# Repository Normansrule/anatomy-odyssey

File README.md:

<div align="center">

# Anatomy Odyssey

**A wall chart of the human body that you can fall into, from two meters down to a single molecule.**

[**Open the web app**](https://normansrule.github.io/anatomy-odyssey/) ·
[Download the desktop app](https://github.com/Normansrule/anatomy-odyssey/releases/latest) ·
[Read the guide](https://normansrule.github.io/anatomy-odyssey/guide/) ·
[Features](#key-features) ·
[Setup](#setup-and-usage) ·
[Design](#design)

<a href="https://normansrule.github.io/anatomy-odyssey/">
<picture>
  <source media="(prefers-color-scheme: dark)" srcset="docs/media/hero-dark.webp" />
  
</picture>
</a>

</div>

## What it is

Anatomy Odyssey is a three-dimensional (3D) model of the human body, drawn like the anatomy charts that hung in every biology classroom, except this one zooms. Grab the scale on the left and drag: the view falls from the whole body (measured from a real person) into an organ, its tissue, one of its cells and finally the molecule that does the work, every plate at its real size. It's made for curious people, students and teachers who want to *see* how the body fits together across scales, not memorize a diagram. It runs in any current browser (phones included) or as a desktop app, with no accounts and no tracking.

> [!NOTE]
> It's a teaching model, not medical advice. Every scene says what it is (a generalized model, drawn to scale unless its card says otherwise) and cites its sources.

## Key features

- **Fifteen dives and six modules.** Skeletal, circulatory, muscular, immune, nervous, respiratory, digestive, urinary, endocrine, skin, eye, ear, pancreas, liver and smell, plus modules on inflammation, gene to protein, body chemistry, immune memory, T cells and the knee-jerk reflex. Every one ends at a molecule.
- **A body measured from a real one.** Meshes from BodyParts3D, an open anatomy atlas: every muscle and organ in its true place. The heart beats, blood flows through the vessels, and the organ close-ups are the real organs cut open.
- **A skeleton you'd find in a lecture hall.** 258 bones and teeth from Z-Anatomy, a finer, cleaned-up rebuild of that atlas, fitted back onto the body to within about a millimeter and shaded with the soft shadow each bone casts on itself: every foramen of the skull, every facet of the spine.
- **Read a heart scan.** A new step turns an ultrasound probe through the four standard echo views, the way trainee doctors learn them with teaching tools like Toronto's Virtual TEE: a fan of sound cuts the real heart, the heart turns to show you the slice, and a scanner screen beside it draws that slice as an echo machine would, grainy and beating, with an ECG running underneath.
- **One slider from 10 m to 0.1 nm.** The scale on the left is a slider. Drag it (or use the arrow keys) and the view zooms continuously, flying on to the next plate whenever you get close to its size, so a single drag can take you from your whole body to DNA.
- **Labeled like a wall chart.** Every part in view is named at the edge of the plate with a line to the part, and numbered in the card's key. Point at a label, a part or a key entry and a red leader line lights up, following the part as the model turns.
- **Zoom in anywhere.** Scroll or pinch toward any part of the body; a guide names the nearest part that has a dive and takes you there.
- **Point, click, learn.** Hover to name a part, click to open its card: what it does, why it matters, its real size, an *Expert detail* switch and a source you can check.
- **Labeled like a lecture-hall chart.** The skeleton names every major bone (skull, jaw, collarbone and shoulder blade, breastbone, humerus, radius, ulna, femur, kneecap, tibia, fibula and the bones of the hand and foot), and the muscular dive names every muscle in the body: the big ones each have a card, and the rest are filed in 20 regional groups the way an atlas's plates are (the face, the jaw, the hyoid, the deep neck, the back, the chest and belly walls, the rotator cuff and shoulder blade, the forearm, hand, hip, thigh, leg and foot), each with what it does and the clinical facts students meet first. The circulatory dive names the vessels by region: the carotid and jugular, subclavian, gut, iliac and limb vessels. Each has its own card, and a chart holds up to 24 labels, set in two balanced columns; an organ dive's chart names its own organs and only a few landmarks around them.
- **By the numbers.** Every whole-body, system and organ plate prints its headline figure under the heading (100,000 heartbeats a day, 86 billion neurons, 480 million alveoli), and the card opens on three big figures that count up as it appears, 64 cards in all, each a typical adult value from the card's sources.
- **Light sheet or slate.** It follows your device's light or dark setting, or pick one in About.
- **Science you can play with.** Sliders run real, tested equations (oxygen binding, nerve speed, blood acidity, how fast an enzyme works, how much blood the heart pumps).
- **A map by scale, a tour, quizzes and a glossary.** The map (press M) lays out every dive on one size axis; the tour narrates a dive with captions you can have read aloud.
- **Front and back plates.** A button under the whole body turns it round, as a wall chart comes as a front and a back plate: the labels move to the parts seen from behind (trapezius, latissimus dorsi, the deep back muscles, the rotator cuff, gluteus maximus, the hamstrings), and each sits on the surface that faces you.
- **Take it apart.** "Take apart" lifts each body system out of the whole and stands them in a row, skin first, then muscle, bone, nerves, blood vessels, lungs, gut, kidneys, glands and the immune system, each on its own floor shadow with its name underneath, the way an exploded diagram lays out a machine. Each figure steps out on a spring, a beat after the one before; "Put together" walks them back in reverse. The row turns round with "See the back" too. Point at a system in the row and it lifts off the floor; each caption gives the system's headline figure and opens its card. Standing alone, the skin fills in to a solid figure. Press A to take it apart and B to turn it round.
- **Named nerves.** The sciatic nerve and its tibial and common fibular branches, the femoral, the brachial plexus, the median, ulnar and radial nerves and both vagus nerves run where they do in life, in atlas yellow, each opening its own card.
- **Sound, if you want it.** Off by default. Turn it on and toggles tick, cards pop, the body breathes as it comes apart, and each plate chimes lower the deeper you go. Every sound is synthesized in the browser, with no files and no downloads.
- **A stage and a measuring rod.** The body stands on a turntable plinth with an engraved dial, beside a stadiometer whose headboard rests on the crown at 1.64 m, and its lungs breathe 14 times a minute.
- **Made to move.** After every flight the plate sets itself like a printed chart: the heading rises out of its baseline and each label's line draws out from its part. The studio light follows your pointer across the model, and the guide's landing page falls through the body as you scroll.
- **A guide website.** A landing page drawn as the same chart, plus the docs as a printed booklet, at [/guide/](https://normansrule.github.io/anatomy-odyssey/guide/).
- **Private and accessible.** No network calls after loading, full keyboard control, screen-reader announcements, a reduced-motion mode, and an automated Web Content Accessibility Guidelines (WCAG) 2.2 audit with zero violations in 55 states, light and dark.

## See it

<table>
<tr>
<td align="center" width="50%"><br /><sub><b>A labeled skeleton.</b> Every major bone named at the plate's edge, the arm and leg bones each with its own card.</sub></td>
<td align="center" width="50%"><br /><sub><b>A labeled muscle chart.</b> Every muscle on the real body opens a card: the big ones their own, the rest their group's.</sub></td>
</tr>
<tr>
<td align="center" width="50%"><br /><sub><b>The back plate.</b> Turn the body round and the chart names what you see from behind.</sub></td>
<td align="center" width="50%"><br /><sub><b>Take it apart.</b> The systems step out of the body one by one and stand in a row, outside in.</sub></td>
</tr>
<tr>
<td align="center" colspan="2"><br /><sub><b>Named nerves.</b> The nerves an anatomy course names first, in atlas yellow, front and back.</sub></td>
</tr>
<tr>
<td align="center" colspan="2"><br /><sub><b>On its stand.</b> A turntable plinth and a stadiometer give the figure a place to stand and a height to read.</sub></td>
</tr>
<tr>
<td align="center" colspan="2"><br /><sub><b>By the numbers.</b> Each plate prints its headline figure, and each card opens on three.</sub></td>
</tr>
<tr>
<td align="center" colspan="2"><br /><sub><b>Read a heart scan.</b> Turn the probe through the four standard views and match each echo picture to the real heart.</sub></td>
</tr>
<tr>
<td align="center" width="50%"><br /><sub><b>258 real bones.</b> Z-Anatomy's skeleton, fitted to the body to a millimeter.</sub></td>
<td align="center" width="50%"><br /><sub><b>One slider, 10 m to 0.1 nm.</b> A single drag takes you from your whole body to DNA.</sub></td>
</tr>
<tr>
<td align="center" colspan="2"><br /><sub><b>Fall through the body.</b> Scroll the guide and drop from your whole body to a strand of DNA.</sub></td>
</tr>
<tr>
<td align="center" colspan="2"><br /><sub><b>The plate sets itself.</b> After every flight the heading rises and each callout draws out from its part.</sub></td>
</tr>
<tr>
<td align="center" colspan="2"><br /><sub><b>The living key.</b> Point at an entry and its leader line draws to the part.</sub></td>
</tr>
<tr>
<td align="center" width="50%"><br /><sub><b>Heartbeat.</b> The measured heart opened to its four chambers; set the rate from asleep to running.</sub></td>
<td align="center" width="50%"><br /><sub><b>The guide.</b> The same chart as a website, with the docs as its booklet.</sub></td>
</tr>
<tr>
<td align="center"><br /><sub><b>Digestion.</b> One meal through the real gut, with how long each part takes.</sub></td>
<td align="center"><br /><sub><b>Urine.</b> From the blood, down the ureters, into the bladder and out.</sub></td>
</tr>
</table>

<table>
<tr>
<td><br /><sub>Whole body</sub></td>
<td><br /><sub>Heart scan</sub></td>
<td><br /><sub>Brain</sub></td>
<td><br /><sub>Lungs</sub></td>
</tr>
<tr>
<td><br /><sub>Liver</sub></td>
<td><br /><sub>Kidney</sub></td>
<td><br /><sub>Femur</sub></td>
<td><br /><sub>Map by scale</sub></td>
</tr>
</table>

### Progress

| Dive | Organ step | What moves | State |
|---|---|---|---|
| Skeletal | measured skeleton (258 Z-Anatomy bones); femur cut open | | Done |
| Circulatory | measured heart, four chambers; heart scan in the four echo views | heartbeat, blood flow, heart rate, the probe turning | Done |
| Respiratory | measured lungs and bronchial tree | breathing | Done |
| Nervous | measured brain, lobes and inside | | Done |
| Digestive | measured tract, esophagus to rectum | a meal moving through | Done |
| Urinary | measured kidneys, ureters and bladder; kidney cut open | urine flow, bladder filling | Done |
| Pancreas | measured pancreas with duct and islets | | Done |
| Liver | measured liver with veins and bile ducts | blood and bile flow | Done |
| Immune | lymph node, drawn | an infection from a cut to the armpit nodes | Body done, close-up drawn |
| Muscular | biceps, drawn and cut across | | Next candidate |
| Skin | skin block, drawn | heat and cold | Drawn close-up |
| Smell | nasal cavity, drawn | a sniff | Drawn close-up |
| Endocrine | thyroid, drawn | | The atlas has no thyroid |
| Eye | eye, drawn | light focusing | The atlas eye is too coarse |
| Ear | ear, drawn | sound | The atlas has the outer ear only |

<details>
<summary><b>More screenshots</b>: every organ, cell and molecule step</summary>

<table>
<tr>
<td></td>
<td></td>
<td></td>
</tr>
<tr>
<td></td>
<td></td>
<td></td>
</tr>
<tr>
<td></td>
<td></td>
<td></td>
</tr>
<tr>
<td></td>
<td></td>
<td></td>
</tr>
<tr>
<td></td>
<td></td>
<td></td>
</tr>
<tr>
<td></td>
<td></td>
<td></td>
</tr>
<tr>
<td></td>
<td></td>
<td></td>
</tr>
<tr>
<td></td>
<td></td>
<td></td>
</tr>
<tr>
<td></td>
<td></td>
<td></td>
</tr>
<tr>
<td></td>
<td></td>
<td></td>
</tr>
<tr>
<td></td>
<td></td>
<td></td>
</tr>
<tr>
<td></td>
<td></td>
<td></td>
</tr>
<tr>
<td></td>
<td></td>
<td></td>
</tr>
<tr>
<td></td>
<td></td>
<td></td>
</tr>
</table>

| Nervous dive | Respiratory dive |
|---|---|
|  |  |

</details>

## Setup and usage

### Just use it

| Version | Where | Notes |
|---|---|---|
| **Web** | [normansrule.github.io/anatomy-odyssey](https://normansrule.github.io/anatomy-odyssey/) | Any current browser, phones included. Nothing to install. |
| **Desktop** | [Latest release](https://github.com/Normansrule/anatomy-odyssey/releases/latest) | Windows `.exe`/`.msi`, macOS `.dmg`, Linux `.AppImage`/`.deb`. Not code-signed yet, so the first launch shows a warning. |

Pick a dive from the menu at the top (or a part of you on the first screen). Then either drag the scale on the left, or use **Dive deeper** and **Zoom out** on the row of plates at the bottom. Scroll or pinch to zoom, drag the view to turn it, and point at a number in the key to see where that part is. Press **M** for the map, and try **Play tour** for a narrated run-through.

| Key | What it does |
|---|---|
| Arrow keys or Page Up and Page Down on the scale | Zoom by a quarter (or a whole) power of ten |
| Home and End on the scale | Jump to 10 m or to 0.1 nm |
| Left and right arrows elsewhere | The previous or next plate |
| `/` | Search |
| `M`, `G`, `T` | The map, the glossary, the tour |

### Run it yourself

You'll need [Node.js](https://nodejs.org) 20 or newer.

```bash
git clone https://github.com/Normansrule/anatomy-odyssey.git
cd anatomy-odyssey
npm ci
npm run dev          # then open http://localhost:5173
```

<details>
<summary><b>More commands</b>: tests, builds, desktop app, screenshots</summary>

```bash
npm test               # 528 unit tests, plus the asset manifest check
npm run build          # production build in dist/ (what GitHub Pages serves), with the guide in dist/guide/
npm run build:preview  # one self-contained HTML (HyperText Markup Language) file in dist-preview/
npm run molecules      # regenerate molecule geometry (needs: pip install rdkit)
python3 tools/record-hero.py --dive skeletal --slide 1e-8 --width 860 --out docs/media/scale-slider.gif
                       # record a README animation (see the file for the other modes; needs Playwright)
python3 tools/build_body_meshes.py --fetch && python3 tools/build_body_meshes.py && npm run manifest
                       # rebuild the body anatomy from BodyParts3D (needs: pip install numpy fast-simplification)
python3 tools/zanatomy_skeleton.py --fetch && python3 tools/zanatomy_skeleton.py
python3 tools/build_body_meshes.py --skeleton tools/sources/zanatomy/skeleton.npz --from-bundle && npm run manifest
                       # swap in Z-Anatomy's skeleton with baked shading (needs: pip install bpy==4.2.0, Python 3.11)
```

**Desktop app** (needs [Rust](https://rustup.rs); on Linux also `sudo apt install libwebkit2gtk-4.1-dev build-essential libssl-dev libayatana-appindicator3-dev librsvg2-dev`):

```bash
npm run desktop:dev      # native window with live reload
npm run desktop:build    # installers in src-tauri/target/release/bundle/
```

Pushing a version tag (`git tag v0.22.0 && git push origin v0.22.0`) builds Windows, macOS and Linux installers and publishes them as a GitHub release. They aren't code-signed yet.

**Headless checks** (software rendering, no graphics card needed):

```bash
npm run build && npx vite preview --port 4173 &
pip install playwright pillow && python3 -m playwright install chromium
python3 tools/screenshots.py --mobile    # every step; fails on console errors or a blank view
python3 tools/a11y-audit.py              # axe-core accessibility audit, WCAG 2.2 A and AA, app and guide, light and dark
python3 tools/shoot-guide-body.py        # redraw the guide's body picture and measure where each dive starts on it
python3 tools/shoot-guide-fall.py        # redraw the cut-out plates for the guide's "Fall through the body"
python3 tools/record-motion.py fall      # record the README's motion animations (fall, plate, scan or skeleton)
python3 tools/shoot-readme-hero.py       # redraw the README's poster, light and dark
```

**Web address options**: `?dive=nervous&step=synapse` opens a step, `&trip=1` opens a side trip, `?renderer=webgl` forces the WebGL 2 fallback, `?env=0` turns off studio reflections.

**Publishing**: [docs/PUBLISHING.md](docs/PUBLISHING.md) has the exact terminal commands to apply a change, push it, turn on GitHub Pages and publish the desktop apps.

</details>

## Project structure

```
src/
  main.js      app start-up: wires the engine, the scenes and the interface together
  engine/      renderer (WebGPU, with a WebGL 2 fallback), tier engine, lighting, device check
    textures/  tissue surfaces generated in code: tileable noise, tissue recipes, materials
  scenes/      one builder per step (body, femur, heart, neuron, lungs, …) plus the registry
  library/     shared building blocks (nucleus, DNA, hemoglobin, ATP, …) and molecule data
  data/        dives, library graph, cards, quizzes, references: all the content lives here
  science/     pure, tested math: scale, equations, chemistry, immune model, T cells, reflexes
  ui/          scale slider, living key, cards, search, controls, tour, quiz, glossary, map, about
  styles/      app.css, the whole visual system (tokens at the top)
guide/         the guide website's stylesheet, script and body picture
src-tauri/     desktop shell (Tauri 2)
assets/        the measured body and molecule files, with credits
tests/         Vitest suites
tools/         guide builder, its Markdown converter and body picture, screenshots, accessibility audit,
               animation recorder, mesh and molecule builders
docs/          state of the model, equations, security model, publishing, media
```

Each dive is a **chain of scenes**, each built at its own scale (1 unit = 1 m for the body, 1 cm for organs, 1 µm for cells, 1 nm or 1 Å for molecules), because the gap from body to molecule is about a billion-fold. The engine frames each scene by its real size and flies between them while the scale slider sweeps on a log scale.

<details>
<summary><b>Adding a dive</b></summary>

1. Write scene builders in `src/scenes/` (return `root`, `metersPerUnit`, `view`, `focus`, `dispose`; optionally `controls`, `update`, `branchFocus`).
2. Register them in `src/scenes/registry.js` and add the dive to `src/data/dives.js`.
3. Tag tissue materials for realistic surfaces: `M(color, { tissue: 'muscle' })` (the kinds are in `src/engine/textures/tissues.js`).
4. Write cards with sources, narration for each step, and four quiz questions.
5. `npm test` checks that frames shrink and tiers rise, every clickable part has a card, and shared steps reuse the library.

</details>

## Design

**The idea: a classroom wall chart.** You know the ones: a pull-down anatomy chart with heavy rules, numbered leader lines running to a key, and the parts colored by a code every textbook shares. Anatomy Odyssey is that chart, with two things paper can't do: the specimen is a live 3D model, and the chart zooms.

- **The sheet is ruled into cells.** The scale column on the left, the plate in the middle, the key on the right, and the plates of the dive along the bottom, all divided by 2-pixel rules like a printed chart. The plate itself sits inside a double-ruled frame, under a heading set the way a chart prints one: a red rubric ("Plate 2 of 6 · Organ tier"), the subject in huge condensed capitals, and the dive it belongs to. No floating cards, no frosted glass, no drop shadows.
- **Every color means something anatomical.** Artery red, vein blue, nerve yellow, lymph green and bone ivory, the code anatomy charts have always used. Red also means "you are here": the scale's marker, the current plate, the one main action and the leader line you're tracing. Vein blue marks focus and links. Nothing gets a color just to decorate.
- **Light sheet or slate.** Light mode is the printed sheet: warm, uncoated paper with a fine grain. Dark mode is the same chart on slate. Every text color is at least 4.5 to 1 against its background in both.
- **Two typefaces, each with one job.** Archivo, condensed and heavy, for plate titles and numbers, like the lettering on a chart; Atkinson Hyperlegible Next, designed for low-vision readers, for everything you read. Nothing is smaller than 12 pixels, and numbers are tabular so they don't jitter while the slider moves.
- **One spacing rhythm.** Every gap is a multiple of 4 pixels, and every target you can press is at least 24 pixels (44 for the main controls).

**The hero moment is the scale slider.** Drag it and the view follows your finger seamlessly: inside a plate the camera zooms on a spring (on a log scale, so every power of ten takes the same time), and when the size you're asking for is closer to the next plate's, the view flies on and keeps going. The flight speeds up out of one plate and slows into the next, so there's no stop in the middle where the model swaps.

**The second is the living key.** On a wide screen the plate is labeled the way a printed chart is: every part's name is set in a column at the plate's edge, with a hairline running to a dot on the part. The labels are projected from the 3D parts every frame, stacked a row apart and centered on their parts so the lines stay short, and they follow the model as you turn it. Point at a label or a key entry and its line turns red; on a phone each part carries a numbered mark instead.

**Then the plate sets itself.** Big product pages earn their polish with motion that explains: a scroll that tells a story, light that answers the pointer, type that arrives instead of appearing. The chart borrows those, in its own printed voice. The neatline rules itself around the plate on the first visit. After every flight the heading rises out of its own baseline and the callouts draw out from their parts one by one, each label reading in from the end its line arrives at, so your eye goes from the part to its name. The studio lights ride with the camera like a photographer's, and the key light leans toward your pointer, so highlights slide across the model as you explore. On the guide, "Fall through the body" pins a stage to the screen and lets your scroll drive the dive: each plate grows past you and fades as the next, smaller one rises out of it, while a needle falls down the ruler and the view height counts down.

**Motion has a job or it doesn't happen.** Buttons answer a press with a slight 0.97 scale in 140 milliseconds, easing out so they feel immediate. Hover effects only switch on for a real mouse, so taps never leave a stuck highlight. With reduced motion on, flights become a short crossfade, the slider and leader lines jump instead of springing, headings and callouts simply appear, the light stays put, the guide shows its plates as a plain row, and nothing slides or scales, but color and fade feedback stay so you still see what happened.

**States are designed too.** Loading shows a ruled "Drawing the plate" title card while the 15 megabyte body loads; if the measured body can't load, a notice says the simplified figure is showing; a browser without 3D graphics gets a plain explanation instead of a blank page; and an empty search suggests what to try.

The whole visual system is the token block at the top of [`src/styles/app.css`](src/styles/app.css), and the guide website reads its tokens from the same file.

## Documentation

All of these are also on the [guide website](https://normansrule.github.io/anatomy-odyssey/guide/), set as the chart's booklet.

| Document | What's inside |
|---|---|
| [State of the model](docs/STATE_OF_THE_MODEL.md) | Every step, where it honestly stops, and what is simplified |
| [Equations](docs/EQUATIONS.md) | 29 worked examples, each with symbols, units and its test |
| [Security model](docs/SECURITY_MODEL.md) | Trust boundaries, privacy (a strict Content Security Policy, no analytics), supply chain |
| [Publishing](docs/PUBLISHING.md) | Apply a change, push it, turn on the website, publish the desktop apps |
| [Changelog](CHANGELOG.md) | What changed in each version |
| [Asset credits](assets/CREDITS.md) | Sources and licenses |

## Roadmap

- [x] Fifteen dives, six modules and a complete shared library; every dive and every module ends at a molecule
- [x] Desktop app, device check, accessibility audit
- [x] Realistic tissue surfaces with natural and stain looks
- [x] A body measured from a real one, and real organs for the heart, brain, lungs, liver, pancreas, kidney, femur and the digestive and urinary tracts
- [x] A wall chart redesign: the scale slider, the living key, light and dark sheets, and a guide website
- [ ] Measured thyroid, eye and ear
- [ ] Real atomic structures from the Protein Data Bank for the large molecules
- [ ] Code-signed desktop releases

## License

- **Code**: [MIT License](LICENSE).
- **Anatomy assets** in `assets/anatomy/`: derived from BodyParts3D, Creative Commons Attribution-ShareAlike 2.1 Japan (CC BY-SA 2.1 JP), with the skeleton from Z-Anatomy by Lluís Vinent and Gauthier Kervyn (CC BY-SA 4.0); see [assets/CREDITS.md](assets/CREDITS.md). ShareAlike covers those files only.
- **Molecular assets**: each file's own license, listed in [assets/CREDITS.md](assets/CREDITS.md).
- **Fonts**: Archivo and Atkinson Hyperlegible Next, SIL Open Font License 1.1, served from the app itself.
- Tissue textures are generated in code and covered by the MIT License.

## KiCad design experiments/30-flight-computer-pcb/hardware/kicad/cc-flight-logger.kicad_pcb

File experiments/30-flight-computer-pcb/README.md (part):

# 30 · Flight-computer PCB — a hand-solderable rocket data logger in KiCad

**Level 3 · stage 3** — design, build and test **CC-FL1**, an 80 × 30 mm printed circuit board that
rides inside a 38 mm airframe and records a rocket flight at 100 samples per second: a Bosch BMP390
barometer, an ST LSM6DSO32 ±32 g inertial measurement unit (IMU), a microSD card, a Li-Po charger,
a beeper and a header for the LoRa radio of [experiment 31](../31-lora-telemetry-ground-station/).
The brain is a **Raspberry Pi Pico** soldered flat by its castellated edge, so there is no
0.4 mm-pitch microcontroller to solder. You get a complete KiCad project generated from one Python
file, firmware with a Kalman filter and a flight state machine, a host-side test harness that
"flies" the real firmware through synthetic flights, and a 3D-printed sled.

It is the natural next step after [experiment 22](../22-barometric-altimeter-payload/) (Pico + BMP390
on a breadboard, MicroPython): same idea, now as a real board, in C++, with sensor fusion.

| Cost | Time | Difficulty | Ages |
|---|---|---|---|
| **$45–110** (boards $5–25, parts $30–45, optional sensor assembly $15–30, Li-Po + card $12) | **20–35 h** (routing 3–5 h, assembly 3 h, firmware + tests 6 h, flight day) | ●●●●○ | 15+; flights at a club launch |

> [!CAUTION]
> **This is a data logger, not a recovery controller.** The board has no outputs that fire anything,
> and none should be added. If a flight needs electronic recovery deployment, that is done by a
> **certified commercial altimeter**, and flying such rockets requires high-power certification and
> mentorship ([experiment 40](../40-high-power-rocketry-certification/)). Fly only
> **commercially certified motors**, at a club launch under a Range Safety Officer, following the NAR or
> Tripoli safety code ([../SAFETY.md](../SAFETY.md)). Li-Po cells: charge on a non-flammable surface,
> never puncture or short them, and store them at ~3.8 V.

## What you'll learn

- **Schematic capture and PCB layout in KiCad**, from a design described as *data* (`design.py`) —
  symbols, footprints, nets, net classes, design-rule checks (DRC), and why placement decides routing.
- **Power design** for a battery gadget: USB-C sink detection, a linear Li-Po charger,
  diode OR-ing, a low-dropout (LDO) regulator, dropout and thermal budgets.
- **Sensor physics**: why a barometer measures altitude, what an accelerometer *really* measures
  (specific force, not acceleration), and how the two are fused with a **Kalman filter**.
- **Real-time firmware** on a dual-core RP2040: a 100 Hz control loop on core 0, a lock-free queue to
  a microSD writer on core 1, a flight **state machine**, and a non-blocking beeper.
- **Testing without flying**: a physics-based synthetic flight generator and a C++ host harness that
  runs the exact firmware logic against ground truth — the way aerospace flight software is tested.
- **Manufacturing**: generating gerbers, choosing assembly options at JLCPCB/PCBWay, reflowing
  land-grid-array (LGA) sensors.

## What is in this folder

```text
30-flight-computer-pcb/
├── hardware/
│   ├── kicad/                  KiCad project (cc-flight-logger.kicad_pro/.kicad_sch/.kicad_pcb)
│   │   ├── cosmic_codex.kicad_sym   project symbols: Pico, BMP390, LSM6DSO32
│   │   └── cosmic_codex.pretty/     project footprints: Pico (hand-solder), BMP390 LGA-10
│   ├── scripts/
│   │   ├── design.py           ← the single source of truth: parts, pins → nets, placement
│   │   ├── make_library.py     writes the project symbols/footprints
│   │   ├── generate.py         writes schematic, board (via KiCad's pcbnew) and BOM.csv
│   │   ├── check.py            asks KiCad for the netlist + DRC and verifies them against design.py
│   │   ├── plot_board.py       placement + ratsnest picture
│   │   └── export_fab.sh       gerbers / drill / pick-and-place / BOM (after routing, KiCad 8+)
│   ├── BOM.csv                 bill of materials with manufacturer + LCSC/DigiKey numbers
│   ├── cc-flight-logger-schematic.pdf
│   ├── ROUTING.md              the routing exercise, step by step
│   └── ORDERING.md             JLCPCB / PCBWay ordering and assembly guide
├── firmware/
│   ├── flight_logger/          Arduino-Pico sketch: flight_logger.ino, flight_core.{h,cpp}, config.h,
│   │                           nmea.h, telemetry_packet.h
│   └── test/                   host test harness (make), mock Arduino headers
├── cad/avionics_sled.scad      OpenSCAD sled for a 38 mm tube  → stl/avionics_sled.stl, stl/nose_bulkhead.stl
├── tools/synth_flight.py       synthetic flight + sensor generator
├── tools/plot_flight.py        plot any flight log
├── data/                       a synthetic flight (sensor input, truth, and the replayed log)
└── images/
```

## System overview

```mermaid
flowchart LR
    USBC["USB-C<br/>(charge only)"] -->|VBUS_C| D1[SS14]
    D1 -->|VBUS| CHG["MCP73831<br/>Li-Po charger<br/>213 mA"]
    PICOUSB["Pico micro-USB<br/>(program + data)"] -->|VBUS| CHG
    CHG -->|+BATT| BAT[("1S Li-Po<br/>JST-PH")]
    BAT --> SW["J3 arming<br/>switch"]
    SW -->|VBAT_SW| D2[SS14] -->|VSYS| PICO["Raspberry Pi Pico<br/>RP2040"]
    D2 -->|VSYS| LDO["AP2112K<br/>3.3 V, EN = GP22"]
    LDO -->|+3V3| BARO["BMP390<br/>barometer"]
    LDO -->|+3V3| IMU["LSM6DSO32<br/>±32 g IMU"]
    LDO -->|+3V3| SD[("microSD")]
    PICO <-->|"I2C0 400 kHz"| BARO
    PICO <-->|I2C0| IMU
    PICO <-->|"SPI0"| SD
    PICO -->|"SPI1"| RADIO["J5 → RFM95W<br/>(exp. 31)"]
    PICO <-->|UART0| GPS["J6 → GPS"]
    PICO -->|GP15| BZ["piezo beeper"]
    PICO -->|GP14| LED[status LED]
    SW -->|"÷2"| PICO
```

## Bill of Materials

Full list with footprints and distributor numbers: [`hardware/BOM.csv`](hardware/BOM.csv) (generated
from `design.py`). Prices are typical single-quantity US prices in 2026 — check on the day.

| Ref | Qty | Part | Manufacturer part number (MPN) | LCSC | Approx. |
|---|---|---|---|---|---|
| U1 | 1 | Raspberry Pi Pico (Pico W also fits) | SC0915 | — (buy from an approved reseller) | $4 |
| U3 | 1 | 6-axis IMU, ±32 g, LGA-14L 2.5 × 3 mm | ST LSM6DSO32TR | search MPN | $4–6 |
| U4 | 1 | Barometer, LGA-10 2 × 2 mm | Bosch BMP390 | search MPN | $3–5 |
| U2 | 1 | Li-Po charger 4.20 V, SOT-23-5 | Microchip MCP73831T-2ACI/OT | C424093 | $0.70 |
| U5 | 1 | 3.3 V 600 mA LDO, SOT-23-5 | Diodes Inc AP2112K-3.3TRG1 | C51118 | $0.30 |
| J1 | 1 | USB-C receptacle, 6-pin power-only | GCT USB4125-GF-A | search MPN | $0.80 |
| J4 | 1 | microSD socket, push-push, card detect | Hirose DM3AT-SF-PEJM5 | search MPN | $1.50 |
| J2 | 1 | JST-PH 2-pin vertical header | JST B2B-PH-K-S(LF)(SN) | search MPN | $0.20 |
| J3, J7 / J6 / J5 | 2 / 1 / 1 | 2.54 mm SMD pin headers 1×2 / 1×4 / 1×8 | generic | — | $1 |
| BZ1 | 1 | piezo sounder 4 kHz, 12 × 12 mm SMD | Murata PKLCS1212E4001-R1 | search MPN | $1.50 |
| Q1 | 1 | NPN transistor, SOT-23 | MMBT3904 | C20526 | $0.05 |
| D1, D2 | 2 | Schottky 40 V 1 A, SMA | SS14 | C2480 | $0.10 |
| D4 | 1 | switching diode, SOD-123 | 1N4148W | C81598 | $0.05 |
| D3 / D5 | 1 / 1 | LED 0805 green / red | KT-0805G / KT-0805R | C2297 / C84256 | $0.10 |
| R1–R16 | 16 | 0805 resistors 1 %: 5.1k ×2, 4.7k ×3, 1k ×4, 100k ×3, 10k ×4 | UNI-ROYAL 0805W8F… | C27834 · C17673 · C17513 · C17407 · C17414 | $0.50 |
| C1–C11 | 10 | 0805 MLCC: 4.7 µF ×2, 10 µF ×2, 1 µF ×1, 100 nF ×5 | Samsung CL21… | C1779 · C15850 · C28323 · C49678 | $0.50 |
| — | 1 | 1S Li-Po 3.7 V ≈ 400 mAh, 8 × 25 × 40 mm ("802540"), with protection circuit, JST-PH lead | — | — | $6–10 |
| — | 1 | microSD card 4–32 GB, "industrial"/high-endurance preferred | — | — | $6–10 |
| — | 2 | M2 × 6 mm screws; 2 × M3 or #4-40 threaded rod for the av-bay | — | — | $2 |
| — | ~15 g | PETG or ASA filament for the sled | — | — | $0.50 |

**Tools**: temperature-controlled soldering iron with a fine chisel tip, flux, 0.5 mm solder wire,
tweezers, a multimeter, a loupe; for the sensors either a small hot plate + solder paste + stencil, a
hot-air station, or the fab's assembly service ([ORDERING.md](hardware/ORDERING.md)).

## The science

### 1. Altitude from pressure

In a hydrostatic atmosphere pressure falls with height as $dp = -\rho g\,dh$. With the International
Standard Atmosphere (ISA) troposphere — temperature $T = T_0 - L h$, $T_0 = 288.15$ K,
$L = 0.0065$ K/m — this integrates to the **pressure altitude**

$$
h(p) = \frac{T_0}{L}\left[1-\left(\frac{p}{p_0}\right)^{\frac{R L}{g M}}\right]
      = 44\,330.8\ \text{m}\left[1-\left(\frac{p}{101\,325\ \text{Pa}}\right)^{0.190263}\right].
$$

The logger reports **altitude above the pad**, $h_{AGL} = h(p) - h(p_{pad})$. Subtracting two pressure
altitudes matters: plugging the pad pressure straight into the formula instead of 101 325 Pa silently
assumes the pad is at sea-level temperature and over-reads by 1.4 % at a 600 m site and 3.5 % at
1500 m. The host test harness caught exactly that bug during development (see `flight_core.cpp`).

Sensitivity: $\left|dh/dp\right| = 1/(\rho g) \approx 0.083$ m/Pa near sea level, so the BMP390's
≈ 3 Pa relative accuracy is ≈ 0.25 m — the datasheet's figure.

### 2. What an accelerometer measures

An accelerometer measures **specific force** $\vec f = \vec a - \vec g$ (acceleration minus gravity), in
units of $g$. Standing on the pad it reads $+1\,g$ along the nose axis even though nothing accelerates;
in free fall at apogee it reads $\approx 0$. So the vertical acceleration of a rocket flying nose-up is

$$ a = (f_{axial} - 1)\,g_0 . $$

After apogee the rocket hangs at an arbitrary angle under its parachute, so the firmware switches to the
magnitude $|\vec f|$, which is ≈ 1 g at a steady descent rate whatever the attitude.

### 3. Fusing the two: a 3-state Kalman filter

State $\mathbf{x} = [h,\ v,\ a]^T$, constant-acceleration model driven by random *jerk*:

$$
\mathbf{x}_{k+1} = F\,\mathbf{x}_k + \mathbf{w},\qquad
F = \begin{bmatrix}1 & \Delta t & \tfrac12\Delta t^2\\ 0 & 1 & \Delta t\\ 0&0&1\end{bmatrix},\qquad
Q = \sigma_j^2\begin{bmatrix}\tfrac{\Delta t^5}{20} & \tfrac{\Delta t^4}{8} & \tfrac{\Delta t^3}{6}\\
\tfrac{\Delta t^4}{8} & \tfrac{\Delta t^3}{3} & \tfrac{\Delta t^2}{2}\\ \tfrac{\Delta t^3}{6} & \tfrac{\Delta t^2}{2} & \Delta t\end{bmatrix}
$$

Predict: $\hat{\mathbf x}^- = F\hat{\mathbf x}$, $P^- = FPF^T + Q$. Each measurement $z$ of one state
component $i$ (barometer → $h$, accelerometer → $a$) is then applied as a scalar update:

$$
K = \frac{P^-_{:,i}}{P^-_{ii} + r},\qquad \hat{\mathbf x} = \hat{\mathbf x}^- + K\,(z - \hat x^-_i),\qquad
P = P^- - K\,P^-_{i,:}
$$

$r$ is the measurement variance: $\sigma_b^2 = (0.6\text{ m})^2$ for the barometer and
$\sigma_a^2 = (0.8\text{ m/s}^2)^2$ for the accelerometer. The ratio of $Q$ to $r$ decides how much the
filter trusts the model versus the sensors. Near Mach 1 the shock waves around the airframe corrupt
static pressure, so above 150 m/s the barometer's $\sigma_b$ is multiplied by 30 (**"Mach lockout"**) and
the filter coasts on the accelerometer.

Velocity is never measured directly — it is *inferred* from the two sensors, and apogee is simply the
moment the inferred velocity crosses zero.

### 4. The state machine

```mermaid
stateDiagram-v2
    [*] --> PAD : calibrate ground pressure (1 s average)
    PAD --> BOOST : |a| > 2.5 g for 100 ms<br/>or (h > 30 m and v > 15 m/s)
    BOOST --> COAST : Kalman a < 0 for 5 samples<br/>(or 8 s timeout)
    COAST --> APOGEE : v ≤ 0 for 5 samples, after 0.5 s<br/>or 10 m below max altitude
    APOGEE --> DESCENT : next sample (it is an event)
    DESCENT --> LANDED : altitude within 2 m for 5 s<br/>and |v| < 1 m/s
    LANDED --> [*] : close file, beep apogee forever
```

Every threshold has a reason: 100 ms of high acceleration rejects a knock on the launch rail (the test
harness injects one); the backup barometric launch detection saves the flight if the IMU fails; the
0.5 s coast lockout rejects transonic pressure glitches; the landed window tolerates wind rocking the
rocket on the ground. On the pad the ground reference follows slow weather drift with a 30 s time
constant, and the last 1 s of pad data is kept in RAM and written at liftoff, so the log starts
*before* first motion.

### 5. Power budget

| Load | Current |
|---|---|
| Pico at 125 MHz, both cores busy | ≈ 25 mA |
| LSM6DSO32 at 416 Hz high-performance | ≈ 0.6 mA |
| BMP390 at 100 Hz, ×4 oversampling | ≈ 0.7 mA |
| microSD writing (average; peaks ~100 mA) | ≈ 20–40 mA |
| LEDs, divider, beeper average | ≈ 3 mA |
| **Total** | **≈ 50–70 mA** |

A 400 mAh cell gives $t \approx 0.8 \times 400/60 \approx 5$ h — plenty for a long day on the pad.
The charger's current is set by one resistor: $I_{REG} = 1000\text{ V}/R_{PROG} = 1000/4700 = 213$ mA
(≈ 0.5 C for this cell). The charger is linear, so it dissipates
$P = (V_{DD}-V_{BAT})\,I \approx (4.65-3.7)(0.213) = 0.20$ W; at ≈ 230 °C/W for SOT-23-5 that is a
46 °C rise — warm, safe. The LDO's dropout is ≈ 25 mV at 60 mA, but the OR-ing Schottky D2 drops
≈ 0.3 V, so the sensor rail stays at 3.3 V while $V_{BAT} \gtrsim 3.65$ V (most of a Li-Po's
capacity). Below that it sags gently; the sensors run down to 1.7 V, microSD cards to 2.7 V.

The USB-C port uses two **5.1 kΩ pull-down resistors** ($R_d$) on CC1/CC2: that is how a USB-C *sink*
tells a charger "I am a device, please turn on 5 V". Without them a C-to-C cable delivers nothing.

### 6. Why 4.7 kΩ I2C pull-ups?

At 400 kHz Fast-mode the bus rise time must be under 300 ns: $t_r \approx 0.847\,R_pC_b$. With
$C_b \approx 50$ pF (two sensors, short tracks), $R_p = 4.7$ kΩ gives ≈ 200 ns. ✔

## Build it — step by step

### A. Generate and inspect the design (30 min)

1. Install **KiCad 8** (or 9) and Python 3.9+. On Linux `sudo apt install kicad` also provides the
   `pcbnew` Python module the generator uses; on Windows/macOS run the scripts with KiCad's bundled
   Python ("KiCad Command Prompt").
2. Regenerate everything and verify it:
   ```bash
   cd hardware/scripts
   python3 make_library.py    # project symbols + footprints
   python3 generate.py        # schematic, board, BOM.csv
   python3 check.py           # KiCad netlist == design.py, DRC summary
   python3 plot_board.py      # images/pcb-placement.png
   ```
   `check.py` exports the netlist *with KiCad itself* and verifies all 166 connected pins against
   `design.py`, then runs KiCad's DRC: expect **0 errors other than "unconnected items"** (routing is
   your job) and some cosmetic silkscreen warnings.
3. Open `hardware/kicad/cc-flight-logger.kicad_pro`. Read the schematic block by block (the numbers
   match the headings in the drawing). Open the PCB editor and the 3D viewer.

### B. Route the board (3–5 h)

Follow **[hardware/ROUTING.md](hardware/ROUTING.md)**. The placement is done for you:

| KiCad render, top (F.Cu + silk) | Bottom (mirrored) |
|---|---|
|  |  |

### C. Order (1 week of waiting)

Run `hardware/scripts/export_fab.sh` and follow **[hardware/ORDERING.md](hardware/ORDERING.md)** —
JLCPCB or PCBWay, 1.6 mm, ENIG, with or without assembly of the two LGA sensors.

### D. Assemble (3 h) — in this order, testing as you go

1. **Sensors first** (they need reflow): U3, U4 by hot plate/hot air, or arrive fab-assembled.
2. **Power section**: J1, R1, R2, D1, U2, R3, R4, D5, C1, C2. Plug in USB-C *without* a battery:
   the red LED may flicker (no battery = charger hunting) — that is normal. Measure 4.6–5.0 V on the
   VBUS side of C1.
3. **Battery path**: J2, J3 (fit a jumper), D2, U5, C3, C4, R10. Connect the Li-Po; **check polarity
   first**. With EN held low by R10 the +3V3 rail should read 0 V — the firmware switches it on.
4. **Everything else** on the bottom: J4 microSD, R13–R16, C9, C10, BZ1, Q1, R5–R7, D3, D4, headers.
5. **The Pico last**, flat on its pads (tack two opposite corners, check alignment, then drag-solder).
6. Clean off flux with isopropyl alcohol; inspect every joint with the loupe.

### E. Firmware (1 h)

1. Arduino IDE 2 → *File → Preferences → Additional boards manager URLs*:
   `https://github.com/earlephilhower/arduino-pico/releases/download/global/package_rp2040_index.json`.
   Install **"Raspberry Pi Pico/RP2040/RP2350"** by Earle Philhower in the Boards Manager.
2. Library Manager: **Adafruit BMP3XX Library**, **Adafruit LSM6DS** (and **LoRa** by Sandeep Mistry
   if you enable telemetry).
3. Open `firmware/flight_logger/flight_logger.ino`, board *Raspberry Pi Pico*, hold **BOOTSEL** while
   plugging the Pico's micro-USB, *Upload*.
4. Serial Monitor at 115200: `CC-FL1 ready. ground 101234.5 Pa, logging to LOG000.CSV`, and the beeper
   gives a double chirp every 3 s. Error beeps: **2 long = barometer, 3 = IMU, 4 = microSD**.

### F. Bench tests (1 h)

1. **Host tests first** (no hardware needed):
   ```bash
   cd firmware/test && make
   ```
   This compiles `flight_core.cpp` with `-Wall -Wextra -Werror`, runs unit tests (ISA altitude, beep
   encoder, Kalman convergence, NMEA parser, telemetry CRC), generates four synthetic flights
   (nominal; rail knock + deployment shock; 3× sensor noise; 1500 m launch site), replays each through
   `FlightComputer`, and checks the detected events against the simulator's truth:
   ```text
   truth:    launch 5.00  burnout 6.90  apogee 20.41 s @ 1135.5 m  landed 87.83
   detected: launch 5.01  burnout 6.90  apogee 20.43 s @ 1135.4 m  landed 92.73
   PASS
   ...
   ALL TESTS PASSED (0 failures)
   sketch compiles against the mock Arduino API (with and without telemetry)
   ```
2. **Pad (orientation) test**: stand the board nose-up for 10 s, then pull the card and look at
   `ax_g/ay_g/az_g`. The axis reading ≈ +1.00 g must be the one set in `config.h`
   (`AXIAL_AXIS`, `AXIAL_SIGN`); fix the config if not. A mis-set axis is the #1 cause of "it never
   detected launch".
3. **Altitude-in-a-jar test**: put the powered logger in a jar with a hand vacuum pump (a brake-bleeder
   pump is ideal) and pull ~50 hPa: the log's `baro_alt_m` should climb ~400 m. Release slowly.
4. **Endurance**: leave it logging on the pad for 2 h on battery; check `vbat_v` and that the file is
   intact.

### G. Fly it (a club launch)

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
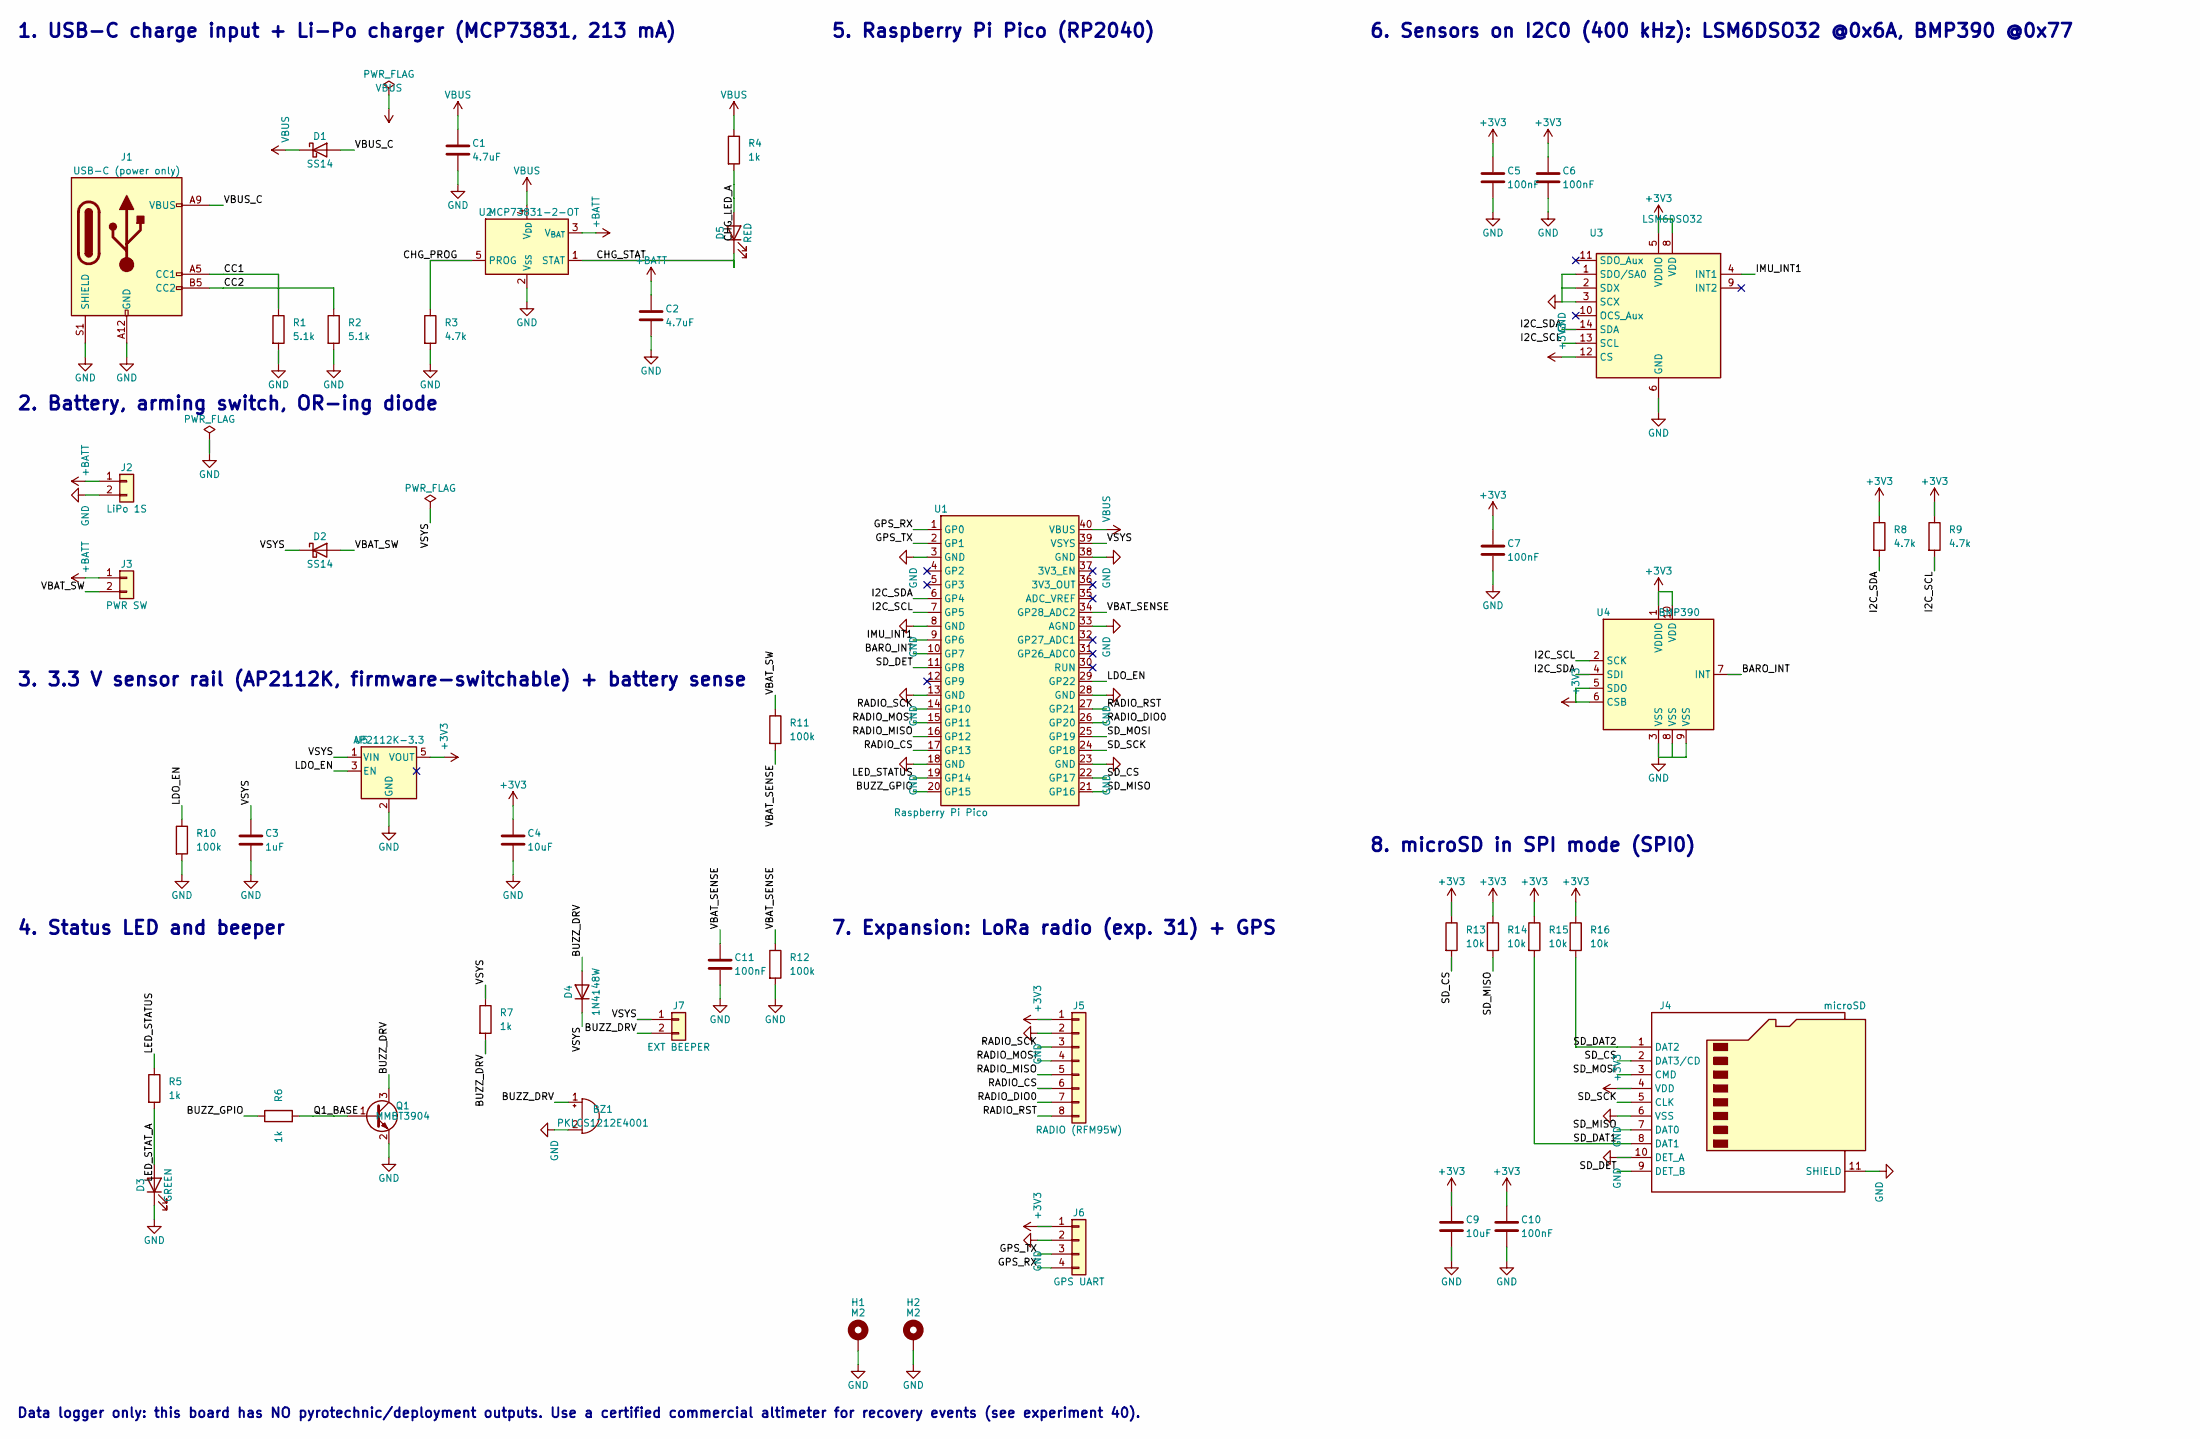
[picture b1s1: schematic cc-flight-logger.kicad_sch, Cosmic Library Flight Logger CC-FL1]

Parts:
BZ1: PKLCS1212E4001; Buzzer_Murata_PKLCS1212E; MPN PKLCS1212E4001-R1
C1, C2: 4.7uF; C_0805_2012Metric_Pad1.18x1.45mm_HandSolder; MPN CL21A475KAQNNNE; LCSC C1779
C3: 1uF; C_0805_2012Metric_Pad1.18x1.45mm_HandSolder; MPN CL21B105KAFNNNE; LCSC C28323
C4, C9: 10uF; C_0805_2012Metric_Pad1.18x1.45mm_HandSolder; MPN CL21A106KAYNNNE; LCSC C15850
C5, C6, C7, C10, C11: 100nF; C_0805_2012Metric_Pad1.18x1.45mm_HandSolder; MPN CL21B104KBCNNNC; LCSC C49678
D1, D2: SS14; D_SMA; MPN SS14; LCSC C2480
D3: GREEN; LED_0805_2012Metric_Pad1.15x1.40mm_HandSolder; MPN KT-0805G; LCSC C2297
D4: 1N4148W; D_SOD-123; MPN 1N4148W; LCSC C81598
D5: RED; LED_0805_2012Metric_Pad1.15x1.40mm_HandSolder; MPN KT-0805R; LCSC C84256
H1, H2: M2; MountingHole_2.2mm_M2_Pad
J1: USB-C (power only); USB_C_Receptacle_GCT_USB4125-xx-x_6P_TopMnt_Horizontal; MPN USB4125-GF-A; DigiKey 2073-USB4125-GF-ACT-ND
J2: LiPo 1S; JST_PH_B2B-PH-K_1x02_P2.00mm_Vertical; MPN B2B-PH-K-S(LF)(SN); DigiKey 455-1704-ND
J3: PWR SW; PinHeader_1x02_P2.54mm_Vertical_SMD_Pin1Left; MPN 2.54 mm 1x02 SMD header
J4: microSD; microSD_HC_Hirose_DM3AT-SF-PEJM5; MPN DM3AT-SF-PEJM5; DigiKey HR1941CT-ND
J5: RADIO (RFM95W); PinHeader_1x08_P2.54mm_Vertical_SMD_Pin1Left; MPN 2.54 mm 1x08 SMD header
J6: GPS UART; PinHeader_1x04_P2.54mm_Vertical_SMD_Pin1Left; MPN 2.54 mm 1x04 SMD header
J7: EXT BEEPER; PinHeader_1x02_P2.54mm_Vertical_SMD_Pin1Left; MPN 2.54 mm 1x02 SMD header
Q1: MMBT3904; SOT-23; MPN MMBT3904; LCSC C20526
R1, R2: 5.1k; R_0805_2012Metric_Pad1.20x1.40mm_HandSolder; MPN 0805W8F5101T5E; LCSC C27834
R3, R8, R9: 4.7k; R_0805_2012Metric_Pad1.20x1.40mm_HandSolder; MPN 0805W8F4701T5E; LCSC C17673
R4, R5, R6, R7: 1k; R_0805_2012Metric_Pad1.20x1.40mm_HandSolder; MPN 0805W8F1001T5E; LCSC C17513
R10, R11, R12: 100k; R_0805_2012Metric_Pad1.20x1.40mm_HandSolder; MPN 0805W8F1003T5E; LCSC C17407
R13, R14, R15, R16: 10k; R_0805_2012Metric_Pad1.20x1.40mm_HandSolder; MPN 0805W8F1002T5E; LCSC C17414
U1: Raspberry Pi Pico; RaspberryPi_Pico_Castellated_HandSolder; MPN SC0915; DigiKey 2648-SC0915CT-ND
U2: MCP73831-2-OT; SOT-23-5; MPN MCP73831T-2ACI/OT; LCSC C424093
U3: LSM6DSO32; LGA-14_3x2.5mm_P0.5mm_LayoutBorder3x4y; MPN LSM6DSO32TR
U4: BMP390; Bosch_LGA-10_2x2mm_P0.5mm_BMP390; MPN BMP390
U5: AP2112K-3.3; SOT-23-5; MPN AP2112K-3.3TRG1; LCSC C51118

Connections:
+3V3: C4.1, C5.1, C6.1, C7.1, C9.1, C10.1, J4.4 (VDD), J5.1, J6.1, R8.1, R9.1, R13.1, R14.1, R15.1, R16.1, U3.5 (VDDIO), U3.8 (VDD), U3.12 (CS), U4.1 (VDDIO), U4.5 (SDO), U4.6 (CSB), U4.10 (VDD), U5.5 (VOUT)
+BATT: C2.1, J2.1, J3.1, U2.3 (V_{BAT})
BARO_INT: U1.10 (GP7), U4.7 (INT)
BUZZ_DRV: BZ1.1 (+), D4.2 (A), J7.2, Q1.3 (C), R7.2
BUZZ_GPIO: R6.1, U1.20 (GP15)
CC1: J1.A5 (CC1), R1.1
CC2: J1.B5 (CC2), R2.1
CHG_LED_A: D5.2 (A), R4.2
CHG_PROG: R3.1, U2.5 (PROG)
CHG_STAT: D5.1 (K), U2.1 (STAT)
GND: BZ1.2 (-), C1.2, C2.2, C3.2, C4.2, C5.2, C6.2, C7.2, C9.2, C10.2, C11.2, D3.1 (K), H1.1, H2.1, J1.A12 (GND), J1.B12 (GND), J1.S1 (SHIELD), J2.2, J4.6 (VSS), J4.10 (DET_A), J4.11 (SHIELD), J5.2, J6.2, Q1.2 (E), R1.2, R2.2, R3.2, R10.2, R12.2, U1.3 (GND), U1.8 (GND), U1.13 (GND), U1.18 (GND), U1.23 (GND), U1.28 (GND), U1.33 (AGND), U1.38 (GND), U2.2 (V_{SS}), U3.1 (SDO/SA0), U3.2 (SDX), U3.3 (SCX), U3.6 (GND), U3.7 (GND), U4.3 (VSS), U4.8 (VSS), U4.9 (VSS), U5.2 (GND)
GPS_RX: J6.4, U1.1 (GP0)
GPS_TX: J6.3, U1.2 (GP1)
I2C_SCL: R9.2, U1.7 (GP5), U3.13 (SCL), U4.2 (SCK)
I2C_SDA: R8.2, U1.6 (GP4), U3.14 (SDA), U4.4 (SDI)
IMU_INT1: U1.9 (GP6), U3.4 (INT1)
LDO_EN: R10.1, U1.29 (GP22), U5.3 (EN)
LED_STATUS: R5.1, U1.19 (GP14)
LED_STAT_A: D3.2 (A), R5.2
Q1_BASE: Q1.1 (B), R6.2
RADIO_CS: J5.6, U1.17 (GP13)
RADIO_DIO0: J5.7, U1.26 (GP20)
RADIO_MISO: J5.5, U1.16 (GP12)
RADIO_MOSI: J5.4, U1.15 (GP11)
RADIO_RST: J5.8, U1.27 (GP21)
RADIO_SCK: J5.3, U1.14 (GP10)
SD_CS: J4.2 (DAT3/CD), R13.2, U1.22 (GP17)
SD_DAT1: J4.8 (DAT1), R15.2
SD_DAT2: J4.1 (DAT2), R16.2
SD_DET: J4.9 (DET_B), U1.11 (GP8)
SD_MISO: J4.7 (DAT0), R14.2, U1.21 (GP16)
SD_MOSI: J4.3 (CMD), U1.25 (GP19)
SD_SCK: J4.5 (CLK), U1.24 (GP18)
VBAT_SENSE: C11.1, R11.2, R12.1, U1.34 (GP28_ADC2)
VBAT_SW: D2.2 (A), J3.2, R11.1
VBUS: C1.1, D1.1 (K), R4.1, U1.40 (VBUS), U2.4 (V_{DD})
VBUS_C: D1.2 (A), J1.A9 (VBUS), J1.B9 (VBUS)
VSYS: C3.1, D2.1 (K), D4.1 (K), J7.1, R7.1, U1.39 (VSYS), U5.1 (VIN)

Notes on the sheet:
1. USB-C charge input + Li-Po charger (MCP73831, 213 mA)
2. Battery, arming switch, OR-ing diode
3. 3.3 V sensor rail (AP2112K, firmware-switchable) + battery sense
4. Status LED and beeper
5. Raspberry Pi Pico (RP2040)
7. Expansion: LoRa radio (exp. 31) + GPS
6. Sensors on I2C0 (400 kHz): LSM6DSO32 @0x6A, BMP390 @0x77
8. microSD in SPI mode (SPI0)
Data logger only: this board has NO pyrotechnic/deployment outputs. Use a certified commercial altimeter for recovery events (see experiment 40).

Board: 2 copper layers, 47 parts (22 on the bottom side), 38 nets, no tracks yet.

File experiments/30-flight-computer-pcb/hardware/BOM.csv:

References,Qty,Value,Description,Manufacturer,MPN,Footprint,LCSC,DigiKey,Side,Notes
BZ1,1,PKLCS1212E4001,"Piezo sounder 4 kHz, 12x12 mm SMD",Murata,PKLCS1212E4001-R1,Buzzer_Beeper:Buzzer_Murata_PKLCS1212E,,,bottom,Drive at 4 kHz; J7 accepts a louder external beeper
"C1,C2",2,4.7uF,MLCC 4.7 uF 25 V X5R 0805,Samsung,CL21A475KAQNNNE,Capacitor_SMD:C_0805_2012Metric_Pad1.18x1.45mm_HandSolder,C1779,,top,
C3,1,1uF,MLCC 1 uF 25 V X5R 0805,Samsung,CL21B105KAFNNNE,Capacitor_SMD:C_0805_2012Metric_Pad1.18x1.45mm_HandSolder,C28323,,top,
"C4,C9",2,10uF,MLCC 10 uF 25 V X5R 0805,Samsung,CL21A106KAYNNNE,Capacitor_SMD:C_0805_2012Metric_Pad1.18x1.45mm_HandSolder,C15850,,bottom/top,SD write bursts draw ~100 mA
"C5,C6,C7,C10,C11",5,100nF,MLCC 100 nF 50 V X7R 0805,Samsung,CL21B104KBCNNNC,Capacitor_SMD:C_0805_2012Metric_Pad1.18x1.45mm_HandSolder,C49678,,bottom/top,
"D1,D2",2,SS14,"Schottky diode 40 V 1 A, SMA",MDD,SS14,Diode_SMD:D_SMA,C2480,,top,"Battery -> VSYS OR-ing, as in Pico datasheet section 4.5; Stops the USB-C port back-feeding the Pico micro-USB"
D3,1,GREEN,LED green 0805 (status),Hubei KENTO,KT-0805G,LED_SMD:LED_0805_2012Metric_Pad1.15x1.40mm_HandSolder,C2297,,bottom,
D4,1,1N4148W,Switching diode SOD-123 (flyback for external magnetic beeper),Changjiang,1N4148W,Diode_SMD:D_SOD-123,C81598,,bottom,
D5,1,RED,LED red 0805 (charging),Hubei KENTO,KT-0805R,LED_SMD:LED_0805_2012Metric_Pad1.15x1.40mm_HandSolder,C84256,,top,"On while charging, off when full"
J1,1,USB-C (power only),"USB Type-C receptacle, 6-pin power only, top mount",GCT,USB4125-GF-A,Connector_USB:USB_C_Receptacle_GCT_USB4125-xx-x_6P_TopMnt_Horizontal,,2073-USB4125-GF-ACT-ND,top,Charge/power only; data uses the Pico's micro-USB
J2,1,LiPo 1S,JST PH 2-pin vertical header (battery),JST,B2B-PH-K-S(LF)(SN),Connector_JST:JST_PH_B2B-PH-K_1x02_P2.00mm_Vertical,,455-1704-ND,bottom,CHECK battery lead polarity: + on pin 1
J3,1,PWR SW,2-pin 2.54 mm SMD header: external arming/screw switch,generic,2.54 mm 1x02 SMD header,Connector_PinHeader_2.54mm:PinHeader_1x02_P2.54mm_Vertical_SMD_Pin1Left,,,bottom,Jumper for bench use
J4,1,microSD,microSD push-push socket with card detect,Hirose,DM3AT-SF-PEJM5,Connector_Card:microSD_HC_Hirose_DM3AT-SF-PEJM5,,HR1941CT-ND,bottom,"Bottom side, card slot at the board end"
J5,1,RADIO (RFM95W),8-pin 2.54 mm SMD header: LoRa radio (experiment 31),generic,2.54 mm 1x08 SMD header,Connector_PinHeader_2.54mm:PinHeader_1x08_P2.54mm_Vertical_SMD_Pin1Left,,,bottom,
J6,1,GPS UART,4-pin 2.54 mm SMD header: GPS module (3.3 V UART),generic,2.54 mm 1x04 SMD header,Connector_PinHeader_2.54mm:PinHeader_1x04_P2.54mm_Vertical_SMD_Pin1Left,,,bottom,GPS TX -> Pico GP1 (RX)
J7,1,EXT BEEPER,2-pin 2.54 mm SMD header: optional external magnetic beeper,generic,2.54 mm 1x02 SMD header,Connector_PinHeader_2.54mm:PinHeader_1x02_P2.54mm_Vertical_SMD_Pin1Left,,,bottom,
Q1,1,MMBT3904,"NPN transistor 40 V 200 mA, SOT-23",Changjiang,MMBT3904,Package_TO_SOT_SMD:SOT-23,C20526,,bottom,Low-side buzzer switch
"R1,R2",2,5.1k,Resistor 5.1k 1% 0805,UNI-ROYAL,0805W8F5101T5E,Resistor_SMD:R_0805_2012Metric_Pad1.20x1.40mm_HandSolder,C27834,,top,Sink (UFP) pull-down on CC1; Sink (UFP) pull-down on CC2
"R3,R8,R9",3,4.7k,Resistor 4.7k 1% 0805,UNI-ROYAL,0805W8F4701T5E,Resistor_SMD:R_0805_2012Metric_Pad1.20x1.40mm_HandSolder,C17673,,top,I2C pull-up; I_charge = 1000 V / R_PROG = 213 mA
"R4,R5,R6,R7",4,1k,Resistor 1k 1% 0805,UNI-ROYAL,0805W8F1001T5E,Resistor_SMD:R_0805_2012Metric_Pad1.20x1.40mm_HandSolder,C17513,,bottom/top,Base resistor; Charge LED current ~2 mA; Pull-up: piezo swings ~VSYS peak-to-peak; Status LED ~1.5 mA
"R10,R11,R12",3,100k,Resistor 100k 1% 0805,UNI-ROYAL,0805W8F1003T5E,Resistor_SMD:R_0805_2012Metric_Pad1.20x1.40mm_HandSolder,C17407,,bottom/top,Divider bottom; Divider top; Keeps sensors off until firmware starts
"R13,R14,R15,R16",4,10k,Resistor 10k 1% 0805,UNI-ROYAL,0805W8F1002T5E,Resistor_SMD:R_0805_2012Metric_Pad1.20x1.40mm_HandSolder,C17414,,bottom,Keeps card deselected at boot; SD DAT0 pull-up; Unused DAT1 pull-up; Unused DAT2 pull-up
U1,1,Raspberry Pi Pico,"Raspberry Pi Pico (RP2040, 2 MB flash), castellated module",Raspberry Pi Ltd,SC0915,cosmic_codex:RaspberryPi_Pico_Castellated_HandSolder,,2648-SC0915CT-ND,top,Pico W (SC0918) also fits; GP29/VSYS-sense differs on W
U2,1,MCP73831-2-OT,"Li-ion/Li-Po linear charger 4.20 V, SOT-23-5",Microchip,MCP73831T-2ACI/OT,Package_TO_SOT_SMD:SOT-23-5,C424093,MCP73831T-2ACI/OTCT-ND,top,
U3,1,LSM6DSO32,"6-axis IMU, +/-32 g accel, +/-2000 dps gyro, LGA-14L",STMicroelectronics,LSM6DSO32TR,Package_LGA:LGA-14_3x2.5mm_P0.5mm_LayoutBorder3x4y,,,top,Fine pitch: reflow (hot plate/hot air) or order assembled. SA0=GND -> I2C 0x6A
U4,1,BMP390,"Barometric pressure sensor, LGA-10 2x2 mm",Bosch Sensortec,BMP390,cosmic_codex:Bosch_LGA-10_2x2mm_P0.5mm_BMP390,,,top,Fine pitch: reflow. SDO=VDDIO -> I2C 0x77. Shield from light and airflow with open-cell foam
U5,1,AP2112K-3.3,"600 mA LDO 3.3 V, SOT-23-5",Diodes Inc,AP2112K-3.3TRG1,Package_TO_SOT_SMD:SOT-23-5,C51118,AP2112K-3.3TRG1DICT-ND,top,Firmware can power-cycle sensors + SD via EN

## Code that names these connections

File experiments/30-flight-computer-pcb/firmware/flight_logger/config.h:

// config.h - pins, rates and options for the CC-FL1 flight logger (Raspberry Pi Pico)
#pragma once

// ---------------- pins (see hardware/scripts/design.py for the full map)
#define PIN_GPS_TX_TO_GPS   0    // UART0 TX  -> GPS RX
#define PIN_GPS_RX_FROM_GPS 1    // UART0 RX  <- GPS TX
#define PIN_I2C_SDA         4    // I2C0
#define PIN_I2C_SCL         5
#define PIN_IMU_INT1        6
#define PIN_BARO_INT        7
#define PIN_SD_DET          8    // card-detect switch to GND (use INPUT_PULLUP): LOW = card present
#define PIN_RADIO_SCK       10   // SPI1
#define PIN_RADIO_MOSI      11
#define PIN_RADIO_MISO      12
#define PIN_RADIO_CS        13
#define PIN_LED             14
#define PIN_BUZZER          15   // drives Q1 -> piezo (and optional external beeper)
#define PIN_SD_MISO         16   // SPI0
#define PIN_SD_CS           17
#define PIN_SD_SCK          18
#define PIN_SD_MOSI         19
#define PIN_RADIO_DIO0      20
#define PIN_RADIO_RST       21
#define PIN_LDO_EN          22   // HIGH = sensor + SD rail on
#define PIN_VBAT_ADC        28   // VBAT_SW / 2

// ---------------- sensors
#define BMP390_I2C_ADDR     0x77 // SDO tied to VDDIO
#define LSM6DSO32_I2C_ADDR  0x6A // SA0 tied to GND
// Which accelerometer axis points to the nose, and its sign. Verify with the "pad test" in the
// README: stand the board nose-up, the log's ax/ay/az column on that axis must read about +1.00 g.
#define AXIAL_AXIS          0    // 0 = X, 1 = Y, 2 = Z
#define AXIAL_SIGN          (+1)

// ---------------- logging
#define SAMPLE_PERIOD_US    10000   // 100 Hz
#define PAD_LOG_DIVIDER     100     // on the pad log 1 sample in 100 (1 Hz) ...
#define PRELAUNCH_SAMPLES   100     // ... but keep the last 1 s in RAM and write it at liftoff
#define POST_LANDING_MS     10000   // keep logging this long after LANDED, then close the file
#define RING_RECORDS        512     // core0 -> core1 queue (5 s of flight data)
#define FLUSH_EVERY_MS      500

// ---------------- beeper
#define BEEP_FREQ_HZ        4000    // piezo resonance (Murata PKLCS1212E4001)
#define BEEP_APOGEE_FEET    0       // 1 = report apogee in feet (common at US launches), 0 = metres

// ---------------- telemetry (experiment 31). Requires the "LoRa" library by Sandeep Mistry.
// Regulatory: read experiment 31 before enabling. Default = Part 15 digital-modulation mode
// (500 kHz bandwidth, fixed channel). If you set a CALLSIGN you are operating as an amateur
// station under Part 97 and must follow its rules (station ID every 10 min, no encryption).
#ifndef TELEMETRY_ENABLED
#define TELEMETRY_ENABLED   0
#endif
#define RADIO_FREQ_HZ       915000000L
#define LORA_SF             9
#define LORA_BW_HZ          500000L
#define LORA_TX_DBM         14
#define TELEMETRY_PERIOD_MS 250     // 4 Hz in flight
#define BEACON_PERIOD_MS    2000    // after landing
#define CALLSIGN            ""      // e.g. "N0CALL" when operating under an amateur licence

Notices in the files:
README.md:
License: MIT
experiments/30-flight-computer-pcb/hardware/kicad/cc-flight-logger.kicad_sch:
License: CERN-OHL-P-2.0
